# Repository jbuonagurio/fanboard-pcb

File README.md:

# Fan Control Board Hardware Design

## Schematic

## Bill of Materials

| Designator    | Quantity | Description                                                                             | Manufacturer          | Manufacturer Part Number | Digi-Key Part Number        | 
|:--------------|:--------:|:----------------------------------------------------------------------------------------|:----------------------|:-------------------------|:----------------------------| 
| SW1           | 1        | DIP Switch SPST 3 Position 1mm Pitch 100mA 6V                                           | Nidec Copal           | CVS-03TB                 | 563-1194-1-ND               | 
| U1            | 1        | 33V Bidirectional Flat-Clamp Surge Protection Device                                    | Texas Instruments     | TVS3301DRBR              | 296-53063-1-ND              | 
| U2            | 1        | 60V 800mA Industrial eFuse with Integrated Input and Output Reverse Polarity Protection | Texas Instruments     | TPS26624DRCR             | 296-TPS26624DRCRCT-ND       | 
| U3            | 1        | Non-Isolated PoL Module DC DC Converter Output 3.3V 500mA Input 4V-36V                  | Texas Instruments     | LMZM23600V3SILT          | 296-49458-1-ND              | 
| U4            | 1        | Dual-Band Wireless MCU Module                                                           | Texas Instruments     | CC3235MODASF12MONR       | 296-CC3235MODASF12MONRCT-ND | 
| C1            | 1        | Ceramic Capacitor 1 μF 50V X7R 0805 ±10%                                                | KEMET                 | C0805C105K5RACTU         | 399-7409-1-ND               | 
| C2            | 1        | Ceramic Capacitor 0.0022 μF (2200 pF) 50V C0G/NP0 0805 ±1%                              | KEMET                 | C0805C222F5GACTU         | 399-11167-1-ND              | 
| C3            | 1        | Ceramic Capacitor 10 μF 50V X7R 1210 ±10%                                               | KEMET                 | C1210C106K5RACTU         | 399-11629-1-ND              | 
| C4 C5         | 2        | Ceramic Capacitor 47 μF 10V X5R 1206 ±20%                                               | KEMET                 | C1206C476M8PACTU         | 399-5508-1-ND               | 
| C6 C7 C8      | 3        | Ceramic Capacitor 0.1 μF 10V X7R 0603 ±10%                                              | KEMET                 | C0603C104K8RACTU         | 399-1095-1-ND               | 
| D1            | 1        | ESD Protection Diode Dual 2.3 pF 3.6V ±30kV SOT23-5                                     | Texas Instruments     | ESDS302DBVR              | 296-51110-1-ND              | 
| D2            | 1        | Yellow 590nm LED Indication 1.85V 0603 (1608 Metric)                                    | Kingbright            | APT1608LSYCK/J3-PRV      | 754-1932-1-ND               | 
| D3            | 1        | Blue 470nm LED Indication 2.65V 0603 (1608 Metric)                                      | Kingbright            | APT1608LVBC/D            | 754-1933-1-ND               | 
| J1 	        | 1	       | HLE Socket 2.54mm Pitch 6 Position 30μ" Selective Gold Locking Clip                     | Samtec                | HLE-103-02-S-DV-LC       | HLE-103-02-S-DV-LC-ND       |
| J4            | 1        | Pico-EZmate Header 1.20mm Pitch 4 Position                                              | Molex                 | 078171-0004              | WM4460CT-ND                 | 
| Q1            | 1        | MOSFET Dual N-Channel Small Signal ESD Protection 20V 630mA SC-88                       | onsemi                | NVJD4401NT1G             | NVJD4401NT1GOSCT-ND         | 
| R1            | 1        | Resistor 1 MΩ 1/10W 0603 ±0.5% Thin Film                                                | Yageo                 | RT0603DRD071ML           | 13-RT0603DRD071MLCT-ND      | 
| R9 R10        | 2        | Resistor 3.3 kΩ 1/10W 0603 ±5%                                                          | Vishay Dale           | CRCW06033K30JNEAC        | 541-CRCW06033K30JNEACCT-ND  | 
| R15           | 1        | Resistor 330 Ω 1/10W 0603 ±1%                                                           | Vishay Dale           | CRCW0603330RFKEA         | 541-330HCT-ND               | 
| R16           | 1        | Resistor 220 Ω 1/10W 0603 ±1%                                                           | Vishay Dale           | CRCW0603220RJNEA         | 541-220GCT-ND               | 
| R2            | 1        | Resistor 536 kΩ 1/10W 0603 ±0.1% Thin Film                                              | Yageo                 | RT0603BRD07536KL         | 13-RT0603BRD07536KLCT-ND    | 
| R3            | 1        | Resistor 24 kΩ 1/10W 0603 ±0.5% Thin Film                                               | Yageo                 | RT0603DRD0724KL          | 311-24KDCT-ND               | 
| R5            | 1        | Resistor 13.3 kΩ 1/10W 0603 ±0.5% Thin Film                                             | Yageo                 | RT0603DRD0713K3L         | 311-13.3KDCT-ND             | 
| R6 R7 R11 R12 | 4        | Resistor 100 Ω 1/10W 0603 ±1%                                                           | Vishay Dale           | CRCW0603100RFKEAC        | 541-3951-1-ND               | 
| R8 R13 R14    | 3        | Resistor 10 kΩ 1/10W 0603 ±1%                                                           | Vishay Dale           | CRCW060310K0FKEAC        | 541-5136-1-ND               |

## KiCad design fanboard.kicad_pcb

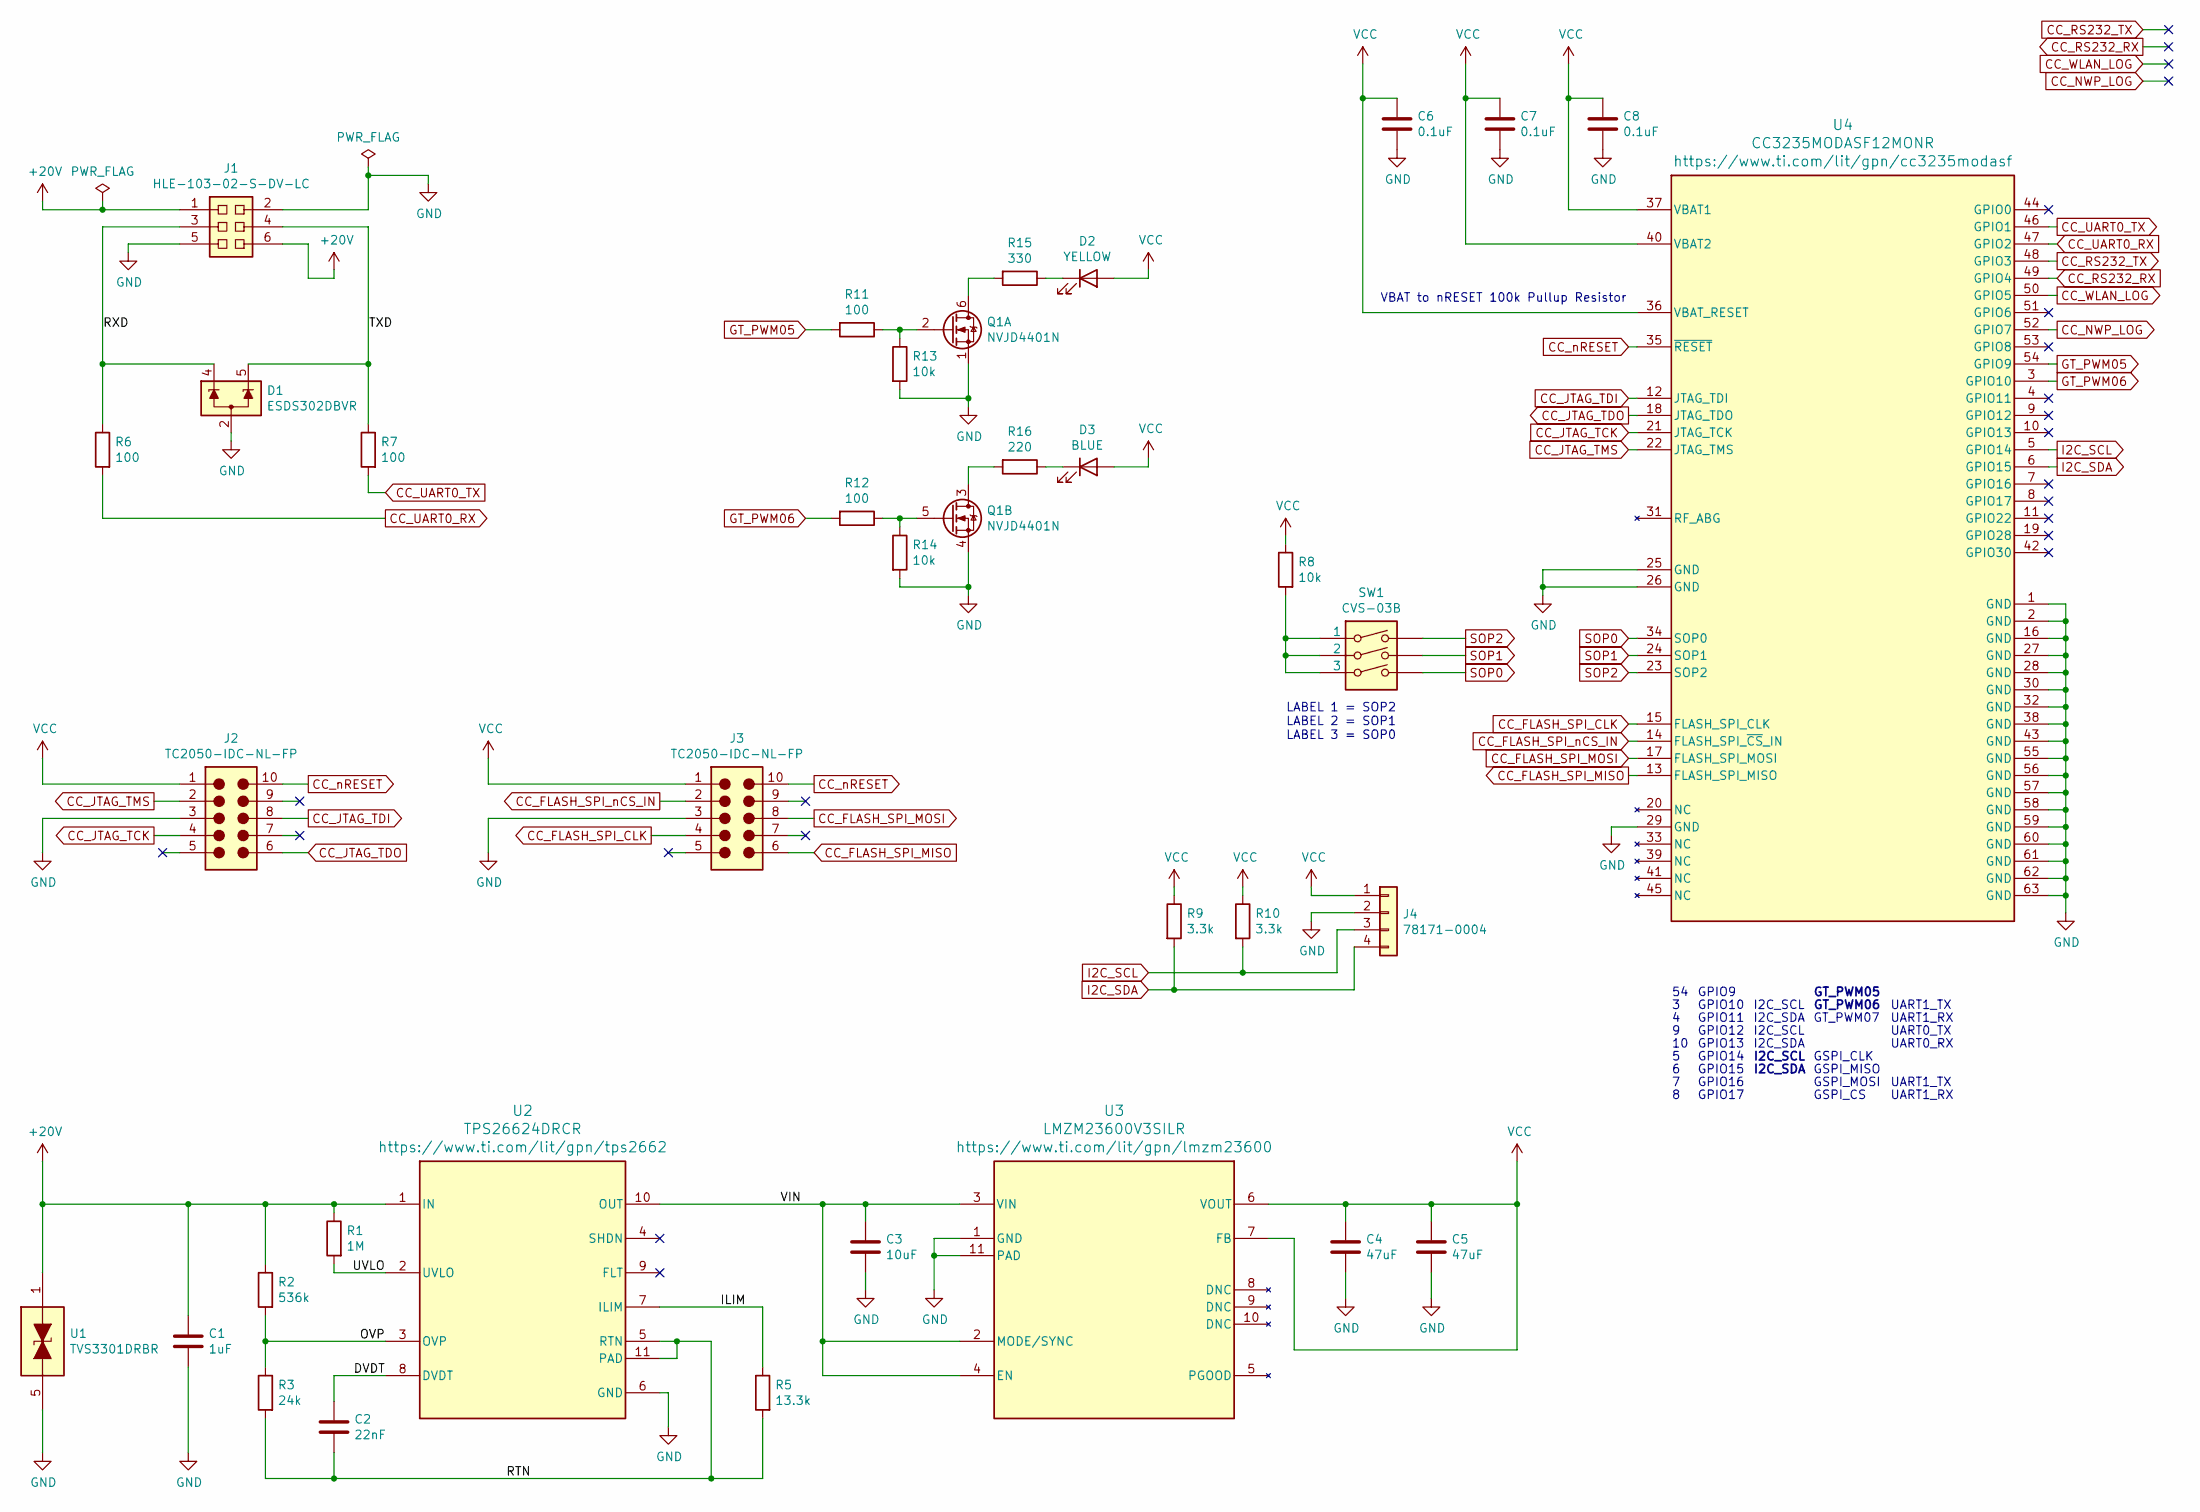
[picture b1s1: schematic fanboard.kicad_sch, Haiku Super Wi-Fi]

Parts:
C1: 1uF; C_0805_2012Metric
C2: 22nF; C_0805_2012Metric
C3: 10uF; C_1210_3225Metric
C4, C5: 47uF; C_1206_3216Metric
C6, C7, C8: 0.1uF; C_0603_1608Metric
D1: ESDS302DBVR; DBV0005A
D2: YELLOW; APT1608
D3: BLUE; APT1608
J1: HLE-103-02-S-DV-LC
J2: TC2050-IDC-NL-FP; TC2050-IDC-NL-FP-JTAG
J3: TC2050-IDC-NL-FP; TC2050-IDC-NL-FP-Flash
J4: 78171-0004
Q1: NVJD4401N; 419B-02
R1: 1M; R_0603_1608Metric
R2: 536k; R_0603_1608Metric
R3: 24k; R_0603_1608Metric
R5: 13.3k; R_0603_1608Metric
R6, R7, R11, R12: 100; R_0603_1608Metric
R8, R13, R14: 10k; R_0603_1608Metric
R9, R10: 3.3k; R_0603_1608Metric
R15: 330; R_0603_1608Metric
R16: 220; R_0603_1608Metric
SW1: CVS-03B
U1: TVS3301DRBR; DRB0008A
U2: TPS26624DRCR; DRC0010J
U3: LMZM23600V3SILR; SIL0010A
U4: CC3235MODASF12MONR; MON0063A

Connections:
+20V: C1.1, J1.1, J1.6, R1.1, R2.1, U1.1 (IN), U1.2 (IN), U1.3 (IN), U1.4 (IN), U2.1 (IN)
/DVDT: C2.1, U2.8 (DVDT)
/ILIM: R5.1, U2.7 (ILIM)
/OVP: R2.2, R3.1, U2.3 (OVP)
/RTN: C2.2, R3.2, R5.2, U2.5 (RTN), U2.11 (PAD)
/RXD: D1.4 (I/O2), J1.3, R6.1
/TXD: D1.5 (I/O1), J1.4, R7.1
/UVLO: R1.2, U2.2 (UVLO)
/VIN: C3.1, U2.10 (OUT), U3.2 (MODE/SYNC), U3.3 (VIN), U3.4 (EN)
CC_FLASH_SPI_CLK: J3.4, U4.15 (FLASH_SPI_CLK)
CC_FLASH_SPI_MISO: J3.6, U4.13 (FLASH_SPI_MISO)
CC_FLASH_SPI_MOSI: J3.8, U4.17 (FLASH_SPI_MOSI)
CC_FLASH_SPI_nCS_IN: J3.2, U4.14 (FLASH_SPI_~CS_IN)
CC_JTAG_TCK: J2.4, U4.21 (JTAG_TCK)
CC_JTAG_TDI: J2.8, U4.12 (JTAG_TDI)
CC_JTAG_TDO: J2.6, U4.18 (JTAG_TDO)
CC_JTAG_TMS: J2.2, U4.22 (JTAG_TMS)
CC_NWP_LOG: U4.52 (GPIO7)
CC_RS232_RX: U4.49 (GPIO4)
CC_RS232_TX: U4.48 (GPIO3)
CC_UART0_RX: R6.2, U4.47 (GPIO2)
CC_UART0_TX: R7.2, U4.46 (GPIO1)
CC_WLAN_LOG: U4.50 (GPIO5)
CC_nRESET: J2.10, J3.10, U4.35 (~RESET)
GND: C1.2, C3.2, C4.2, C5.2, C6.2, C7.2, C8.2, D1.2 (GND), J1.2, J1.5, J2.3, J3.3, J4.2, Q1.1 (S), Q1.4 (S), R13.2, R14.2, U1.5 (GND), U1.6 (GND), U1.7 (GND), U1.8 (GND), U2.6 (GND), U3.1 (GND), U3.11 (PAD), U4.1 (GND), U4.2 (GND), U4.16 (GND), U4.25 (GND), U4.26 (GND), U4.27 (GND), U4.28 (GND), U4.29 (GND), U4.30 (GND), U4.32 (GND), U4.38 (GND), U4.43 (GND), U4.55 (GND), U4.56 (GND), U4.57 (GND), U4.58 (GND), U4.59 (GND), U4.60 (GND), U4.61 (GND), U4.62 (GND), U4.63 (GND)
GT_PWM05: R11.2, U4.54 (GPIO9)
GT_PWM06: R12.2, U4.3 (GPIO10)
I2C_SCL: J4.3, R10.2, U4.5 (GPIO14)
I2C_SDA: J4.4, R9.2, U4.6 (GPIO15)
unnamed: D2.1 (K), R15.1
unnamed: D3.1 (K), R16.1
unnamed: Q1.2 (G), R11.1, R13.1
unnamed: Q1.3 (D), R16.2
unnamed: Q1.5 (G), R12.1, R14.1
unnamed: Q1.6 (D), R15.2
unnamed: R8.2, SW1.1, SW1.2, SW1.3
SOP0: SW1.4, U4.34 (SOP0)
SOP1: SW1.5, U4.24 (SOP1)
SOP2: SW1.6, U4.23 (SOP2)
VCC: C4.1, C5.1, C6.1, C7.1, C8.1, D2.2 (A), D3.2 (A), J2.1, J3.1, J4.1, R8.1, R9.1, R10.1, U3.6 (VOUT), U3.7 (FB), U4.36 (VBAT_RESET), U4.37 (VBAT1), U4.40 (VBAT2)

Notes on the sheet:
GPIO14
UART1_RX
GSPI_CS
GSPI_MISO
GT_PWM07
GPIO10
UART0_RX
GPIO16
GPIO11
I2C_SCL
I2C_SDA
GT_PWM06
UART1_TX
GSPI_MOSI
VBAT to nRESET 100k Pullup Resistor
GPIO15
GPIO12
UART0_TX
GPIO17
LABEL 1 = SOP2 LABEL 2 = SOP1 LABEL 3 = SOP0
GSPI_CLK
GPIO9
GT_PWM05
GPIO13

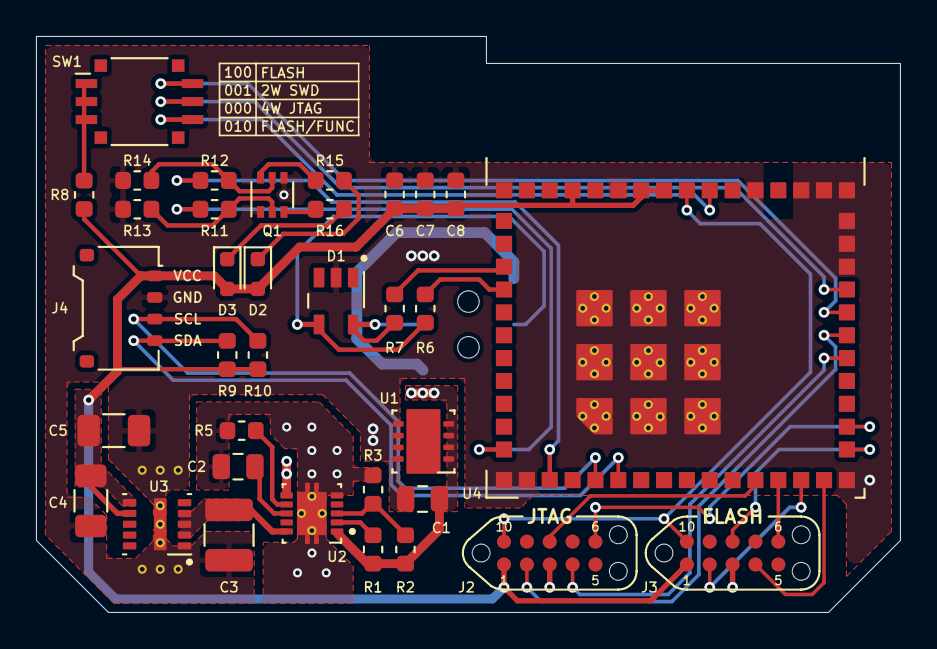
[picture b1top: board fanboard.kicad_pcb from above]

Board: 2 copper layers, 48.0 x 32.0 mm, 36 parts (1 on the bottom side), 36 nets.

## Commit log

2021-12-24 First commit
    First commit
2022-01-15 Update to KiCad 6; add additional manufacturer STEP files.

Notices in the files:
fanboard.kicad_pcb:
© 2021
